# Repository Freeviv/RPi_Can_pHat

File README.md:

# RPi Can pHat
A Raspberry Can pHat/Shield/Addon (Hat only if it has a eeprom memory installed into it). Based on the template from [xesscorp](https://github.com/xesscorp/RPi_Hat_Template).

The current version is 1.2.  
The first two where tests to verify the design (I messed up twice <.<). So if you want to use this design to make sure that you validate it for yourself. If you find something to improve please make sure to create an issue or pull request.

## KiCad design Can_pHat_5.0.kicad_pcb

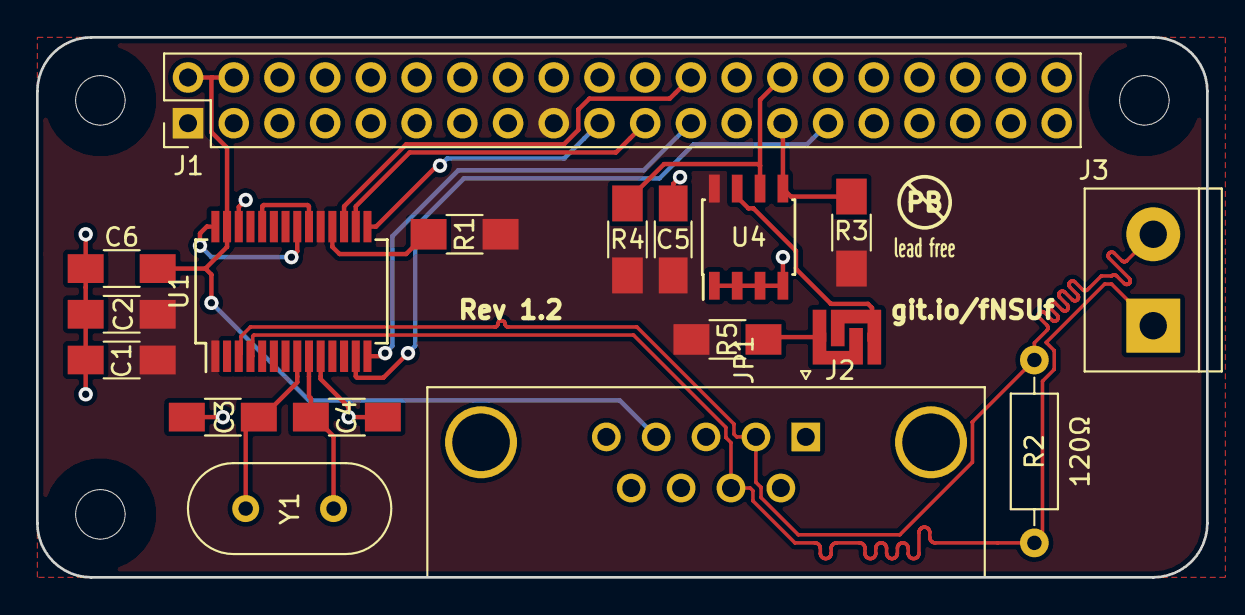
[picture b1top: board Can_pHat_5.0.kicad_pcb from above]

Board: 2 copper layers, 65.0 x 30.0 mm, 18 parts (0 on the bottom side), 19 nets.

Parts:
C1, C2, C6: 0.1uF; C_1206_HandSoldering
C3, C4: 22pF; C_1206_HandSoldering
C5: 100nF; C_1206_HandSoldering
J1: RaspberryPi40PinHeader; Pin_Header_Straight_2x20_Pitch2.54mm
J2: DB9_Female; DSUB-9_Female_Horizontal_P2.77x2.84mm_EdgePinOffset4.94mm_H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
J3: Screw_Terminal_01x02; TerminalBlock_bornier-2_P5.08mm
JP1: Jumper_2_Open; solder_jumper1
R1: 10k; R_1206_HandSoldering
R2: 120R; R_Axial_DIN0207_L6.3mm_D2.5mm_P10.16mm_Horizontal
R3, R4: 3.9k; R_1206_HandSoldering
R5: 1k; R_1206_HandSoldering
U1: MCP25625-x-SS; SSOP-28_5.3x10.2mm_Pitch0.65mm
U4: 24LC01; SOIC-8_3.9x4.9mm_Pitch1.27mm
Y1: 8MHz; Crystal_HC49-U_Vertical

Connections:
+3V3: C1.1, C2.1, C5.1, J1.1, J1.17, R1.1, R3.1, R4.1, R5.1, U1.1, U1.19, U4.8
+5V: C6.2, J1.2, J1.4, J2.4, U1.27
CAN+: J2.7, J3.1, R2.2, U1.4
CAN-: J2.2, J3.2, R2.1, U1.3
GND: C1.2, C2.2, C3.2, C4.2, C5.2, C6.1, J1.6, J1.9, J1.14, J1.20, J1.25, J1.34, J1.39, J2.3, J2.6, U1.10, U1.26, U4.1, U4.2, U4.3, U4.4
ID_SC: J1.28, R4.2, U4.6
ID_SD: J1.27, R3.2, U4.5
unnamed: JP1.1, R5.2
unnamed: JP1.2, U4.7
unnamed: R1.2, U1.18
unnamed: U1.20, U1.24
unnamed: U1.21, U1.28
OSC1: C4.1, U1.9, Y1.1
OSC2: C3.1, U1.8, Y1.2
SCK: J1.23, U1.14
SI: J1.19, U1.15
SO: J1.21, U1.16
~CS: J1.24, U1.17
~INT: J1.29, U1.13

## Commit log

2018-11-23 Init release of v1.3
2018-11-23 Added mediocre README text
2018-11-23 Added license
2019-02-14 Changed IC combination (MCP2515, MCP2551) to a single IC (MCP25625). A smaller solution while maintaining the same cost (Or reducing it on larger volumes).
2019-02-14 Changed Readme Version
    I need to make up my mind with the versioning scheme
